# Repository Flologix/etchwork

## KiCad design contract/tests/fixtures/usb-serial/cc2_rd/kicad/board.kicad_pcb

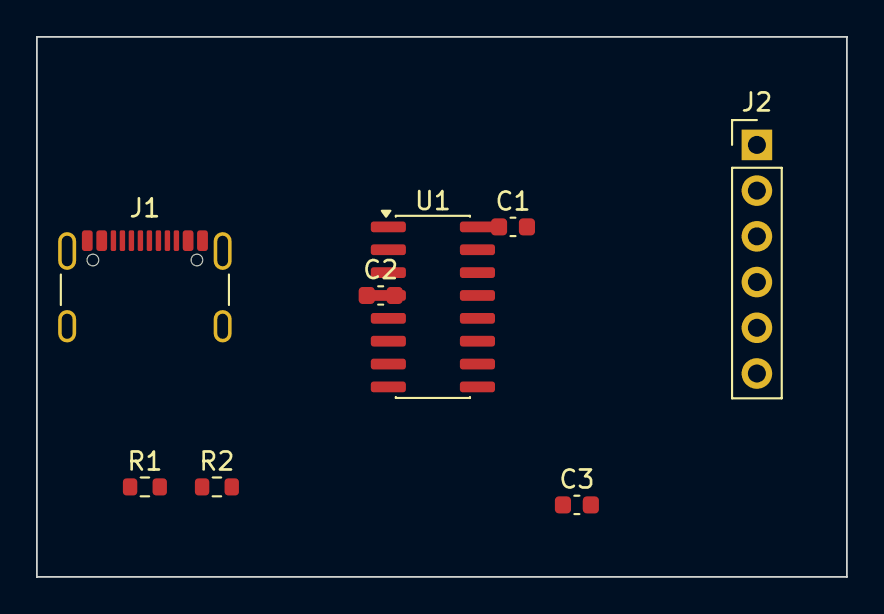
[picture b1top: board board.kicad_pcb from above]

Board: 2 copper layers, 45.0 x 30.0 mm, 8 parts (0 on the bottom side), 11 nets, no tracks yet.

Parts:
C1, C2, C3: 100n; C_0603_1608Metric
J1: USB_C_Receptacle_USB2.0_16P; USB_C_Receptacle_GCT_USB4105-xx-A_16P_TopMnt_Horizontal
J2: Conn_01x06; PinHeader_1x06_P2.54mm_Vertical
R1: 5.1k; R_0603_1608Metric
R2: 22k; R_0603_1608Metric
U1: CH340C; SOIC-16_3.9x9.9mm_P1.27mm

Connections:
CC1: J1.A5 (CC1), R1.1
CC2: J1.B5 (CC2), R2.1
D+: J1.A6 (D+), J1.B6 (D+), U1.5 (UD+)
D-: J1.A7 (D-), J1.B7 (D-), U1.6 (UD-)
GND: C1.2, C2.2, J1.A1 (GND), J1.A12 (GND), J1.B1 (GND), J1.B12 (GND), J1.SH (SHIELD), J2.1, R1.2, R2.2, U1.1 (GND)
N_DTR: C3.1, U1.13 (~DTR)
N_RST: C3.2, J2.6
N_RX: J2.5, U1.3 (RXD)
N_TX: J2.4, U1.2 (TXD)
N_V3: C2.1, U1.4 (V3)
VBUS: C1.1, J1.A4 (VBUS), J1.A9 (VBUS), J1.B4 (VBUS), J1.B9 (VBUS), J2.3, U1.16 (VCC)
